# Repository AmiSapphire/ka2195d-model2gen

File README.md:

# ka2195d-model2gen

## Introduction
Project that aims to fix the Model 2 Sega Genesis's composite video clock that uses the console's crystal oscillator instead of using an external one.

This repo contains the schematic, PCBs, and Gerber files for the Composite Video clock fix for Model 2 Sega Genesis consoles: revision VA0, VA1, and VA1.8 boards that contain the infamous Samsung KA2195D NTSC video encoder. The Gerber files can be used for other PCB fabs.

Notes:
* These are KiCad 6 files, so KiCad 5 and earlier will not work with these.
* This does not fix the RGB jailbars, as it is a somewhat different (yet related) issue.
* This particular PCB uses Imperial 1206 size SMD components.
* Removal of the original 10K resistor on R61 on the console's board is **_required_**.
* R61_L is +2.5V as VREF, connecting to SBCR.
* R61_R is GND, connecting to C24, then KA2195 pin 6.

--

## Details
This [twitter thread (through nitter.net)](https://nitter.net/AmiSapphire/status/1496249012688756744) is the original instruction-like thread (with video examples as well). In short:

* you remove R61 from the board
* mount the board to the console's CPU
* have one wire connect to R61's left pad from the R61_L pad
* have one wire connect to R61's right pad from the R61_R pad
* have one wire connect as ground to wherever ground can be, e.g. C4's right pad, C1's left pad

--

## Images
R61 Pad Indicators:

R61 End Result:

--

## OSH Park order links
Original (test): https://oshpark.com/shared_projects/IpuYYXQL

SMD Hand Solder: https://oshpark.com/shared_projects/toKAOWpJ

Through Hole: https://oshpark.com/shared_projects/uN65Pqal

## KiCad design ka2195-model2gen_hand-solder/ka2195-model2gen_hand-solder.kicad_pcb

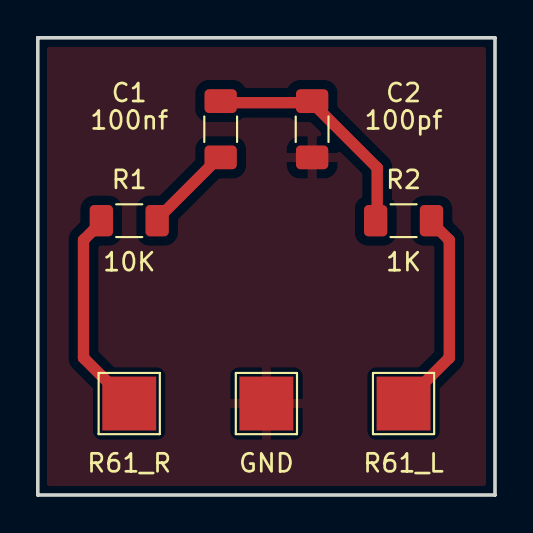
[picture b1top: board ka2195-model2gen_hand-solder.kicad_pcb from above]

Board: 2 copper layers, 25.4 x 25.4 mm, 5 parts (0 on the bottom side), 3 nets.

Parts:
C1: 100nf; C_1206_3216Metric_Pad1.33x1.80mm_HandSolder
C2: 100pf; C_1206_3216Metric_Pad1.33x1.80mm_HandSolder
GND: Earth; TestPoint_Pad_3.0x3.0mm
R1: 10K; R_1206_3216Metric_Pad1.30x1.75mm_HandSolder
R2: 1K; R_1206_3216Metric_Pad1.30x1.75mm_HandSolder

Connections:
Earth: C2.1, GND.1
unnamed: C1.1, R1.2
unnamed: C1.2, C2.2, R2.1

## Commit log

2022-04-16 First upload
2022-04-16 Update README.md
    Short change; will update with links and images soon
2022-04-16 Large update to README.md
    Add twitter thread through nitter proxy, links to OSH Park projects, lots of info, a few images uploaded (one more is needed at R61 end result)
